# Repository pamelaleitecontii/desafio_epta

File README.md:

# Datalogger Ambiental e Inercial com STM32F411

Projeto desenvolvido para o desafio do processo seletivo da Payload, da EPTA (Equipe de Propulsão e Tecnologia Aeroespacial da UFU).

Trata-se de uma placa embarcada no payload de um foguete, responsável por registrar o voo inteiro: temperatura, umidade e pressão do ambiente, além da aceleração e da velocidade angular do veículo. Os dados são gravados em um cartão microSD, em arquivos CSV, para análise posterior.

## Status do projeto

Situação do projeto na entrega do desafio:

- [x] Configuração do microcontrolador no STM32CubeMX 
- [x] Projeto base compilando no STM32CubeIDE, sem erros e sem warnings
- [x] Esquemático no KiCad
- [x] Layout da PCB no KiCad
- [x] Firmware escrito: drivers do BME280 e do LSM6DSO, gravação do CSV e tratamento de erros
- [x] Testes da lógica do firmware no computador
- [x] Compilação do firmware completo no STM32CubeIDE

## Componentes principais

| Bloco | Componente | Interface |
|---|---|---|
| Microcontrolador | STM32F411CEU6 (UFQFPN48) | Não se aplica |
| Temperatura, umidade e pressão | BME280 | I²C |
| IMU (acelerômetro e giroscópio) | LSM6DSO | SPI, com pino de interrupção |
| Armazenamento | Slot microSD | SDIO de 4 bits |
| Alimentação | USB-C com regulador de 3,3 V | Não se aplica |
| Gravação e depuração | Conector SWD | SWDIO e SWCLK |
| Interface com o usuário | LED de status, botão de reset e botão de BOOT0 | GPIO e pinos do MCU |

## Pinagem

A pinagem foi definida no STM32CubeMX, e a configuração completa está no arquivo [`firmware/firmware.ioc`](firmware/firmware.ioc).

Os pinos do LED, dos cristais, do USB e do SWD seguem a mesma disposição da placa WeAct Black Pill, que usa o mesmo microcontrolador. Com isso, o mesmo firmware pode ser validado futuramente em uma Black Pill e rodar na placa projetada sem nenhuma alteração.

### Cartão microSD (SDIO de 4 bits)

| Sinal | Pino | Observação |
|---|---|---|
| CK | PB15 | Clock do cartão |
| CMD | PA6 | Comandos |
| D0 | PB7 | Dados |
| D1 | PA8 | Dados |
| D2 | PA9 | Dados |
| D3 | PB5 | Dados |
| SD_DETECT | PB1 | Detecção de cartão, entrada com pull-up |

### IMU LSM6DSO (SPI1)

| Sinal | Pino | Observação |
|---|---|---|
| SCK | PA5 | Clock do SPI |
| MOSI | PA7 | Dados do microcontrolador para o sensor |
| MISO | PB4 | Dados do sensor para o microcontrolador |
| IMU_CS | PA4 | Seleção do sensor, controlada por software |
| IMU_INT1 | PB0 | Interrupção de dado pronto, borda de subida |

### Sensor BME280 (I2C1)

| Sinal | Pino |
|---|---|
| SCL | PB8 |
| SDA | PB9 |

### USB

| Sinal | Pino |
|---|---|
| D- | PA11 |
| D+ | PA12 |

### Gravação e depuração

| Interface | Sinal | Pino |
|---|---|---|
| SWD | SWDIO | PA13 |
| SWD | SWCLK | PA14 |

### Cristais

| Cristal | Uso | Pinos |
|---|---|---|
| 25 MHz | Clock principal (HSE) | PH0 e PH1 |
| 32,768 kHz | Relógio de tempo real (LSE) | PC14 e PC15 |

### LED

| Função | Pino | Observação |
|---|---|---|
| LED_STATUS | PC13 | Mesmo pino do LED da Black Pill |

## Placa (PCB)

O projeto do KiCad está em [`hardware/datalogger/`](hardware/datalogger/).

| Item | Valor |
|---|---|
| Camadas | 2 (F.Cu e B.Cu) |
| Dimensões | 51,2 × 31,2 mm |
| Plano de terra | GND preenchido nas duas camadas, costurado com vias |
| Trilhas de sinal | 0,2 mm |
| Trilhas de alimentação (VBUS, +3V3, VDDA, GND) | 0,4 mm (classe de rede `Power`) |
| Isolamento mínimo | 0,2 mm |
| Vias | 0,6 mm de diâmetro, furo de 0,3 mm |
| Componentes passivos | 0603 |

**Alimentação:** USB-C (com resistores de 5,1 kΩ no CC1 e no CC2 e blindagem ligada ao GND por 1 MΩ em paralelo com 4,7 nF), proteção ESD com USBLC6-2SC6 nas linhas de dados e regulador AP2112K-3.3 com capacitores de 1 µF na entrada e na saída.

**Microcontrolador:** um capacitor de 100 nF junto de cada pino VDD e do VBAT, capacitor de volume de 4,7 µF, 4,7 µF no VCAP1 e filtro no VDDA (ferrite de 600 Ω a 100 MHz com 1 µF e 100 nF).

**Botões:** reset (NRST) e BOOT0 (com pull-down de 10 kΩ; pressionado durante o reset, coloca o chip no bootloader para gravação pelo USB).

**Pontos de teste:**

| Ponto | Rede |
|---|---|
| TP2 | VBUS |
| TP3 | +3V3 |
| TP10 | VDDA |
| TP5 | GND |
| TP6 | I2C1_SCL |
| TP7 | I2C1_SDA |

## Clock

O clock do sistema vem do cristal externo de 25 MHz, passando pelo PLL.

| Parâmetro | Valor |
|---|---|
| Fonte do PLL | HSE, cristal de 25 MHz |
| Divisores do PLL | M = 25, N = 192, P = 2, Q = 4 |
| Clock do sistema (HCLK) | 96 MHz |
| Barramento APB1 | 48 MHz |
| Barramento APB2 | 96 MHz |
| Clock do USB e do SDIO | 48 MHz |
| RTC | LSE, cristal de 32,768 kHz |

O sistema opera em 96 MHz, e não no máximo de 100 MHz, porque o USB e o SDIO precisam de exatamente 48 MHz. Com um cristal de 25 MHz, 96 MHz é a frequência que permite obter esses 48 MHz exatos a partir do mesmo PLL.

Outras configurações:

- **TIM2** conta de 1 em 1 µs (prescaler de 95). Por ser de 32 bits, só reinicia a contagem depois de cerca de 71 minutos, tempo muito maior que a duração de um voo. É usado nos timestamps de alta resolução.
- **RTC** alimentado pelo cristal de 32,768 kHz, para registrar data e hora reais em cada leitura.
- **FatFs** sobre o SDIO com DMA, com suporte a nomes longos de arquivo.

## Organização do repositório

| Pasta | Conteúdo |
|---|---|
| `hardware/` | Projeto do KiCad (esquemático e PCB) e arquivos de fabricação |
| `firmware/` | Projeto do STM32CubeIDE, gerado pelo STM32CubeMX |
| `docs/` | Decisões de projeto, diagrama de blocos, testes e datasheets |
| `scripts/` | Scripts em Python para análise dos CSVs |
| `tests/` | Testes da lógica do firmware que rodam no computador |

## Firmware

### Organização do código

O código próprio fica em arquivos separados dos gerados pelo CubeMX, e a parte que não depende de hardware fica separada dos drivers. Assim, regenerar o projeto não apaga nada e a lógica pode ser testada no computador.

| Arquivo (`firmware/Core/`) | Função | Depende da HAL? |
|---|---|---|
| `app.c` / `app.h` | Laço principal: leitura dos sensores, linhas do CSV, erros e LED | Sim |
| `bme280.c` / `bme280.h` | Driver do BME280 pelo I2C1 | Sim |
| `bme280_comp.c` / `bme280_comp.h` | Compensação de temperatura, pressão e umidade (fórmulas da Bosch) | Não |
| `lsm6dso.c` / `lsm6dso.h` | Driver do LSM6DSO pelo SPI1 e conversão para mg e mdps | Só o driver |
| `csv_log.c` / `csv_log.h` | Formatação das linhas do CSV | Não |
| `logger.c` / `logger.h` | Gravação no microSD com FatFs | Sim |

### Funcionamento

- **IMU:** 104 Hz, ±16 g e ±2000 dps. A cada amostra nova o sensor gera uma interrupção no INT1 (PB0); a interrupção só sinaliza, e a leitura pelo SPI acontece no laço principal. Se a interrupção parar de chegar por 50 ms, o IMU é lido por polling.
- **BME280:** modo normal, lido a cada 100 ms. A última leitura entra em todas as linhas do CSV.
- **Gravação:** cada amostra do IMU gera uma linha. As linhas se acumulam num buffer de 4 KB e são gravadas em setores inteiros de 512 bytes; `f_sync` é chamado a cada 1 s, então uma queda de energia perde no máximo cerca de 1 s de dados.
- **Arquivos:** cada gravação cria o próximo nome livre (`LOG000.CSV`, `LOG001.CSV`, ...).
- **Início:** a gravação começa sozinha ao ligar a placa, assim que houver cartão.

### Tratamento de erros

| Situação | Como é detectada | Comportamento |
|---|---|---|
| Cartão ausente | Pino SD_DETECT em nível alto | Não grava; tenta de novo a cada 1 s e começa sozinho quando o cartão é inserido |
| Cartão removido durante a gravação | SD_DETECT muda durante a gravação | Descarta o estado do arquivo e volta a esperar o cartão |
| Cartão cheio | `f_write` grava menos bytes que o pedido | Fecha o arquivo com o que já foi gravado e para |
| Falha do IMU | WHO_AM_I diferente de 0x6C ou erro no SPI | Continua gravando o BME280 a 10 Hz, com flag de erro; tenta de novo a cada 1 s |
| Falha do BME280 | ID diferente de 0x60 ou erro no I2C | Continua gravando o IMU, com flag de erro; tenta de novo a cada 1 s |

### LED de status (PC13)

| Padrão | Significado |
|---|---|
| 1 piscada curta por segundo | Gravando, sensores OK |
| 2 piscadas curtas por segundo | Gravando, algum sensor com falha |
| Pisca rápido (100 ms) | Cartão ausente |
| Pisca médio (250 ms) | Erro ao montar ou gravar no cartão |
| Aceso direto | Cartão cheio |

### Formato do CSV

Os valores são gravados como inteiros em unidades pequenas, para não depender de `printf` com ponto flutuante (desligado por padrão na biblioteca C do STM32). O script `scripts/plot_csv.py` converte para as unidades usuais.

| Coluna | Unidade | Exemplo | Valor |
|---|---|---|---|
| `t_s` | segundos desde a inicialização (resolução de 1 µs, TIM2) | `12.345678` | 12,345678 s |
| `rtc` | hora do RTC | `13:07:05` | |
| `ax_mg`, `ay_mg`, `az_mg` | mg | `999` | 0,999 g |
| `gx_mdps`, `gy_mdps`, `gz_mdps` | mdps (milésimos de grau por segundo) | `-70` | -0,07 °/s |
| `temp_cdegC` | centésimos de °C | `2508` | 25,08 °C |
| `press_Pa` | Pa | `100653` | 1006,53 hPa |
| `hum_cpct` | centésimos de %RH | `4523` | 45,23 %RH |
| `flags` | bit 0: erro no IMU; bit 1: erro no BME280 | `2` | BME280 com falha |

### Análise dos dados

```
pip install pandas matplotlib
python scripts/plot_csv.py LOG000.CSV            # abre os gráficos
python scripts/plot_csv.py LOG000.CSV grafico.png # salva em arquivo
```

O script mostra um resumo (duração, taxa de amostragem, linhas com erro, aceleração máxima e altitude barométrica relativa máxima) e plota aceleração, velocidade angular, temperatura, pressão com altitude relativa e umidade.

## Como compilar e gravar o firmware

São necessários o [STM32CubeIDE](https://www.st.com/stm32cubeide) e um gravador ST-Link V2. O [STM32CubeMX](https://www.st.com/stm32cubemx) só é necessário para alterar a configuração do microcontrolador.

Para compilar:

1. Clonar este repositório.
2. No STM32CubeIDE, abrir **File > Import > STM32 > STM32CubeMX/STM32CubeIDE Project**.
3. Selecionar a pasta `firmware` e clicar em **Finish**.
4. Selecionar o projeto e compilar com **Ctrl+B**.

Para gravar, basta ligar o ST-Link ao conector SWD (SWDIO, SWCLK, GND, 3V3 e NRST) e clicar em **Run** no STM32CubeIDE. Para depurar, usar **Debug**.

Para alterar algum pino ou periférico, abrir o `firmware/firmware.ioc` no STM32CubeMX, fazer a alteração e clicar em **GENERATE CODE**. O código escrito dentro dos blocos `USER CODE BEGIN` e `USER CODE END` é preservado.

## Testes

A placa não foi montada fisicamente, e não houve hardware disponível (placa de desenvolvimento ou módulos) para validar o firmware dentro do prazo do desafio.

Por isso, a validação foi feita em duas frentes:

- **Compilação** do firmware completo no STM32CubeIDE.
- **Testes no computador** da parte do firmware que não depende de hardware, em `tests/`.

| Teste | Método | Resultado |
|---|---|---|
| Compilação do projeto base (CubeMX) | STM32CubeIDE | OK, sem erros e sem warnings |
| Compilação do firmware completo | STM32CubeIDE | Pendente |
| Compensação do BME280: exemplo numérico da Bosch | `tests/test_host.c` | OK: 25,08 °C e 100653,25 Pa (esperado: 25,08 °C e 100653,27 Pa) |
| Compensação do BME280: ponto fixo x ponto flutuante | `tests/test_host.c`, varredura de 7 749 combinações | OK: diferença máxima de 0,005 °C, 0,07 Pa e 0,007 %RH |
| Leitura dos coeficientes de calibração (incluindo H4 e H5 negativos) | `tests/test_host.c` | OK |
| Conversão das leituras do IMU | `tests/test_host.c` | OK: 2049 LSB = 999 mg; fundo de escala = 15,99 g e 2293,7 °/s |
| Formatação do CSV | `tests/test_host.c` | OK, inclusive com tempo acima da volta de 32 bits do TIM2 |
| Gravação em setores alinhados de 512 bytes | `tests/test_logger_mock.c`, FatFs simulada | OK: 0 escritas desalinhadas |
| Detecção de cartão cheio e de cartão ausente | `tests/test_logger_mock.c`, FatFs simulada | OK |
| Script de análise | `scripts/plot_csv.py` com CSV sintético | OK |
| Testes em hardware | Não realizado | Sem hardware disponível |

Para rodar os testes (na raiz do repositório, com GCC):

```
gcc -std=c99 -Wall -Wextra -I firmware/Core/Inc tests/test_host.c firmware/Core/Src/bme280_comp.c firmware/Core/Src/csv_log.c -lm -o test_host
./test_host

gcc -std=c11 -Wall -Wextra -I tests/mock -I firmware/Core/Inc tests/test_logger_mock.c firmware/Core/Src/logger.c firmware/Core/Src/csv_log.c -o test_logger
./test_logger
```

### Roteiro de validação em hardware

Roteiro previsto para quando houver hardware disponível, seja a placa montada ou uma Black Pill com módulos em protoboard, na ordem sugerida pelo desafio:

1. Medir a tensão de 3,3 V na saída do regulador.
2. Gravar o firmware pelo SWD e verificar o LED de status piscando.
3. Fazer uma varredura no barramento I²C e confirmar a resposta do BME280.
4. Ler o registrador WHO_AM_I do LSM6DSO pelo SPI.
5. Criar um arquivo no cartão microSD.
6. Testar os erros tratados pelo firmware: sensor desconectado, cartão ausente e cartão cheio.
7. Comparar as leituras do BME280 com um instrumento de referência.
8. Verificar o IMU em repouso, esperando aceleração próxima de 1 g no eixo vertical.

## Decisões de projeto

A justificativa de cada escolha, com as fontes consultadas, está no arquivo [`docs/decisoes-de-projeto.md`](docs/decisoes-de-projeto.md).

## Referências

- STMicroelectronics. STM32F411xC/E Datasheet (DS10314).
- STMicroelectronics. AN4488: Getting started with STM32F4xxxx MCU hardware development.
- STMicroelectronics. UM1718: STM32CubeMX for STM32 configuration and initialization C code generation.
- STMicroelectronics. LSM6DSO Datasheet.
- Bosch Sensortec. BME280 Datasheet (fórmulas de compensação, seção 4.2.3 e apêndice 8).
- Bosch Sensortec. BMP280 Datasheet (exemplo numérico de compensação de temperatura e pressão, usado nos testes).
- ChaN. FatFs: Generic FAT Filesystem Module. http://elm-chan.org/fsw/ff/
- WeAct Studio. MiniF4 (Black Pill), STM32F4x1. https://github.com/WeActTC/MiniF4-STM32F4x1
- EPTA, UFU. Desafio de Processo Seletivo Payload, 11 de outubro de 2026.

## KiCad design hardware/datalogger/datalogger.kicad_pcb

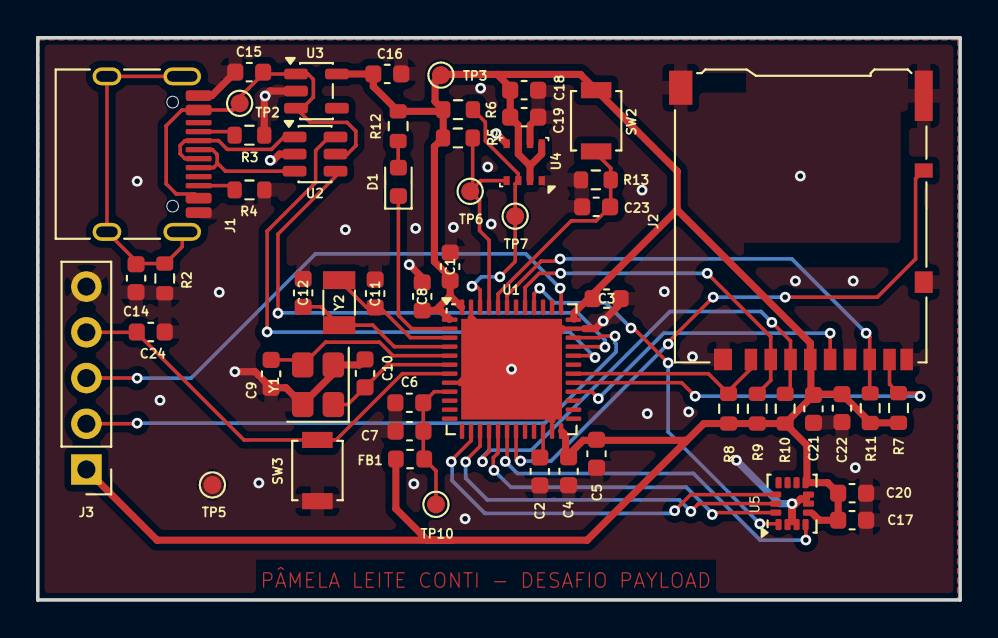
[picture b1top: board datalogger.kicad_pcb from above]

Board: 2 copper layers, 51.2 x 31.2 mm, 55 parts (0 on the bottom side), 36 nets.

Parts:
C1, C3, C4, C7, C8, C17, C18, C19, C20, C21, C23, C24: 100nF; C_0603_1608Metric
C2, C5: 4.7µF; C_0603_1608Metric
C6, C15, C16: 1µF; C_0603_1608Metric
C9, C10: 10pF; C_0603_1608Metric
C11, C12: 4.7pF; C_0603_1608Metric
C14: 4.7nF; C_0603_1608Metric
C22: 10µF; C_0603_1608Metric
D1: LED_Small; LED_0603_1608Metric
FB1: 600R@100MHz; L_0603_1608Metric
J1: USB_C_Receptacle_USB2.0_16P; USB_C_Receptacle_HRO_TYPE-C-31-M-12
J2: Micro_SD_Card_Det_Hirose_DM3AT; microSD_HC_Hirose_DM3AT-SF-PEJM5
J3: Conn_01x05_Pin; PinHeader_1x05_P2.54mm_Vertical
R2: 1M; R_0603_1608Metric
R3, R4: 5.1k; R_0603_1608Metric
R5, R6: 4.7k; R_0603_1608Metric
R7, R8, R9, R10, R11, R13: 10k; R_0603_1608Metric
R12: 1k; R_0603_1608Metric
SW2, SW3: SW_Push; SW_SPST_B3U-1000P
TP2, TP3, TP5, TP6, TP7, TP10: TestPoint; TestPoint_Pad_D1.0mm
U1: STM32F411CEUx; QFN-48-1EP_7x7mm_P0.5mm_EP5.6x5.6mm
U2: USBLC6-2SC6; SOT-23-6
U3: AP2112K-3.3; SOT-23-5
U4: BME280; Bosch_LGA-8_2.5x2.5mm_P0.65mm_ClockwisePinNumbering
U5: LSM6DSO; LGA-14_3x2.5mm_P0.5mm_LayoutBorder3x4y
Y1: 25MHz; Crystal_SMD_3225-4Pin_3.2x2.5mm
Y2: 32.768kHz; Crystal_SMD_3215-2Pin_3.2x1.5mm

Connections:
+3V3: C1.1, C3.1, C4.1, C5.1, C8.1, C16.1, C17.2, C18.2, C19.1, C20.2, C21.1, C22.1, FB1.1, J2.4 (VDD), J3.1, R5.2, R6.2, R7.1, R8.1, R9.1, R10.1, R11.1, R12.1, SW2.2, TP3.1 (1_1), U1.1 (VBAT), U1.24 (VDD), U1.36 (VDD), U1.48 (VDD), U3.5 (VOUT), U4.2 (CSB), U4.6 (VDDIO), U4.8 (VDD), U5.5 (VDDIO), U5.8 (VDD)
/Clock_HSE: C9.2, U1.5 (PH0), Y1.3
/Clock_LSE: C11.2, U1.3 (PC14), Y2.2
/I2C1_SCL: R5.1, TP6.1 (1_1), U1.45 (PB8), U4.4 (SCK)
/I2C1_SDA: R6.1, TP7.1 (1_1), U1.46 (PB9), U4.3 (SDI)
/IMU_CS: U1.14 (PA4), U5.12 (CS)
/IMU_INT1: U1.18 (PB0), U5.4 (INT1)
/LED_STATUS: D1.1 (K), U1.2 (PC13)
/SDIO_CK: J2.5 (CLK), U1.28 (PB15)
/SDIO_CMD: J2.3 (CMD), R10.2, U1.16 (PA6)
/SDIO_D0: J2.7 (DAT0), R11.2, U1.43 (PB7)
/SDIO_D1: J2.8 (DAT1), R7.2, U1.29 (PA8)
/SDIO_D2: J2.1 (DAT2), R8.2, U1.30 (PA9)
/SDIO_D3: J2.2 (DAT3/CD), R9.2, U1.41 (PB5)
/SD_DETECT: J2.10 (DET_A), U1.19 (PB1)
/SPI1_MISO: U1.40 (PB4), U5.1 (SDO/SA0)
/SPI1_MOSI: U1.17 (PA7), U5.14 (SDA)
/SPI1_SCK: U1.15 (PA5), U5.13 (SCL)
/SWCLK: J3.3, U1.37 (PA14)
/SWDIO: J3.2, U1.34 (PA13)
/USB_DM: U1.32 (PA11), U2.6 (I/O1)
/USB_DP: U1.33 (PA12), U2.4 (I/O2)
/VBUS: C15.1, J1.A4 (VBUS), J1.A9 (VBUS), J1.B4 (VBUS), J1.B9 (VBUS), TP2.1 (1_1), U2.5 (VBUS), U3.1 (VIN), U3.3 (EN)
/VDDA: C6.1, C7.1, FB1.2, TP10.1 (1_1), U1.9 (VDDA)
BOOT0: C23.1, R13.1, SW2.1, U1.44 (BOOT0)
GND: C1.2, C2.2, C3.2, C4.2, C5.2, C6.2, C7.2, C8.2, C9.1, C10.2, C11.1, C12.2, C14.2, C15.2, C16.2, C17.1, C18.1, C19.2, C20.1, C21.2, C22.2, C23.2, C24.1, J1.A1 (GND), J1.A12 (GND), J1.B1 (GND), J1.B12 (GND), J2.6 (VSS), J2.9 (DET_B), J2.SH (SHIELD), J3.5, R2.2, R3.2, R4.2, R13.2, SW3.2, TP5.1 (1_1), U1.8 (VSSA), U1.23 (VSS), U1.35 (VSS), U1.47 (VSS), U1.49 (VSS), U2.2 (GND), U3.2 (GND), U4.1 (GND), U4.5 (SDO), U4.7 (GND), U5.2 (SDX), U5.3 (SCX), U5.6 (GND), U5.7 (GND), Y1.2 (G), Y1.4 (G)
unnamed: D1.2 (A), R12.2
unnamed: J1.A5 (CC1), R3.1
unnamed: J1.B5 (CC2), R4.1
unnamed: J1.A6 (D+), J1.B6 (D+), U2.3 (I/O2)
unnamed: J1.A7 (D-), J1.B7 (D-), U2.1 (I/O1)
unnamed: C14.1, J1.SH (SHIELD), R2.1
unnamed: C12.1, U1.4 (PC15), Y2.1
unnamed: C10.1, U1.6 (PH1), Y1.1
unnamed: C2.1, U1.22 (VCAP1)
Reset: C24.2, J3.4, SW3.1, U1.7 (NRST)

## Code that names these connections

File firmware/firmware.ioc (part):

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Mcu.Name=STM32F411C(C-E)Ux
Mcu.Package=UFQFPN48
Mcu.UserName=STM32F411CEUx
PA11.Mode=Device_Only
PA11.Signal=USB_OTG_FS_DM
PA12.Mode=Device_Only
PA12.Signal=USB_OTG_FS_DP
PA13.Mode=Serial_Wire
PA13.Signal=SYS_JTMS-SWDIO
PA14.Mode=Serial_Wire
PA14.Signal=SYS_JTCK-SWCLK
PA4.GPIOParameters=PinState,GPIO_Label
PA4.GPIO_Label=IMU_CS
PA4.PinState=GPIO_PIN_SET
PA4.Signal=GPIO_Output
PA5.Mode=Full_Duplex_Master
PA5.Signal=SPI1_SCK
PA6.Mode=SD_4_bits_Wide_bus
PA6.Signal=SDIO_CMD
PA7.Mode=Full_Duplex_Master
PA7.Signal=SPI1_MOSI
PA8.Mode=SD_4_bits_Wide_bus
PA8.Signal=SDIO_D1
PA9.Mode=SD_4_bits_Wide_bus
PA9.Signal=SDIO_D2
PB0.GPIOParameters=GPIO_Label
PB0.GPIO_Label=IMU_INT1
PB0.Signal=GPXTI0
PB1.GPIOParameters=GPIO_PuPd,GPIO_Label
PB1.GPIO_Label=SD_DETECT
PB1.GPIO_PuPd=GPIO_PULLUP
PB1.Signal=GPIO_Input
PB15.Mode=SD_4_bits_Wide_bus
PB15.Signal=SDIO_CK
PB4.Mode=Full_Duplex_Master
PB4.Signal=SPI1_MISO
PB5.Mode=SD_4_bits_Wide_bus
PB5.Signal=SDIO_D3
PB7.Mode=SD_4_bits_Wide_bus
PB7.Signal=SDIO_D0
PB8.Mode=I2C
PB8.Signal=I2C1_SCL
PB9.Mode=I2C
PB9.Signal=I2C1_SDA
PC13-ANTI_TAMP.GPIOParameters=GPIO_Label
PC13-ANTI_TAMP.GPIO_Label=LED_STATUS
PC13-ANTI_TAMP.Signal=GPIO_Output
PC14-OSC32_IN.Mode=LSE-External-Oscillator
PC14-OSC32_IN.Signal=RCC_OSC32_IN
PC15-OSC32_OUT.Mode=LSE-External-Oscillator
PC15-OSC32_OUT.Signal=RCC_OSC32_OUT
PH0\ -\ OSC_IN.Mode=HSE-External-Oscillator
PH0\ -\ OSC_IN.Signal=RCC_OSC_IN
PH1\ -\ OSC_OUT.Mode=HSE-External-Oscillator
PH1\ -\ OSC_OUT.Signal=RCC_OSC_OUT
RCC.HSE_VALUE=25000000
RCC.SYSCLKFreq_VALUE=96000000
RCC.SYSCLKSource=RCC_SYSCLKSOURCE_PLLCLK
board=custom
